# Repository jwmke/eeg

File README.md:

# Open-Source Affordable EEG PCB

### An 8-channel EEG Pi Pico W shield, based off of OpenBCI's [Cyton Biosensing Board](https://shop.openbci.com/products/cyton-biosensing-board-8-channel), for 1/10th the price.

The heart of this PCB is a Texas Instrument's [ADS1299](https://www.ti.com/product/ADS1299), a low noise, 8-Channel, Analog-to-Digital Converter.

## Instructions
1. Update your SSID and PASSWORD in the pico/main.py file
2. Upload the main.py to the Pi Pico W
3. Run the pico/main.py on the Pico Pi W and note the printed IP
5. Unplug the Pi Pico W from the PC and place it into the PCB
6. Update the PICO_IP in the computer/plot_data.py file
7. Run the computer/plot_data.py on a PC
8. Plug a 3.7V Lipo battery into the PCB
9. Blinking LED == Connecting, Solid LED == Succesfully streaming to PC

## Schematics

## Layout

Top

Bottom

Ground

AVSS/-2.5V

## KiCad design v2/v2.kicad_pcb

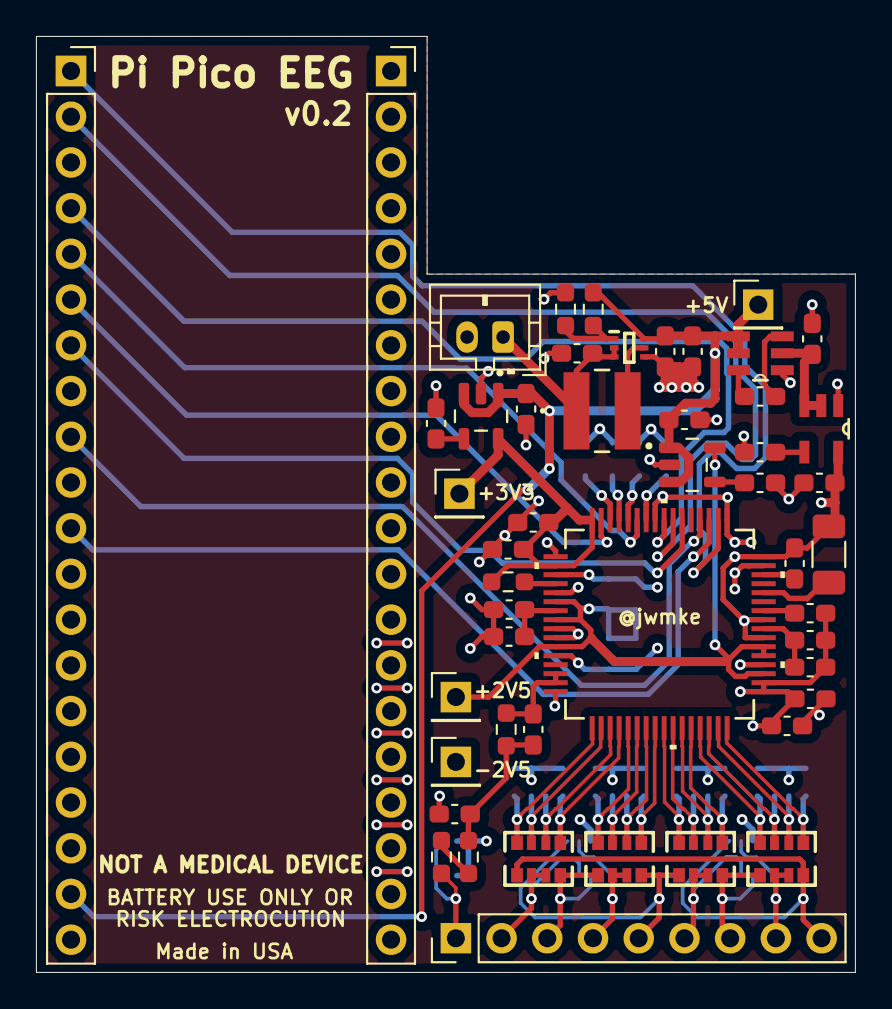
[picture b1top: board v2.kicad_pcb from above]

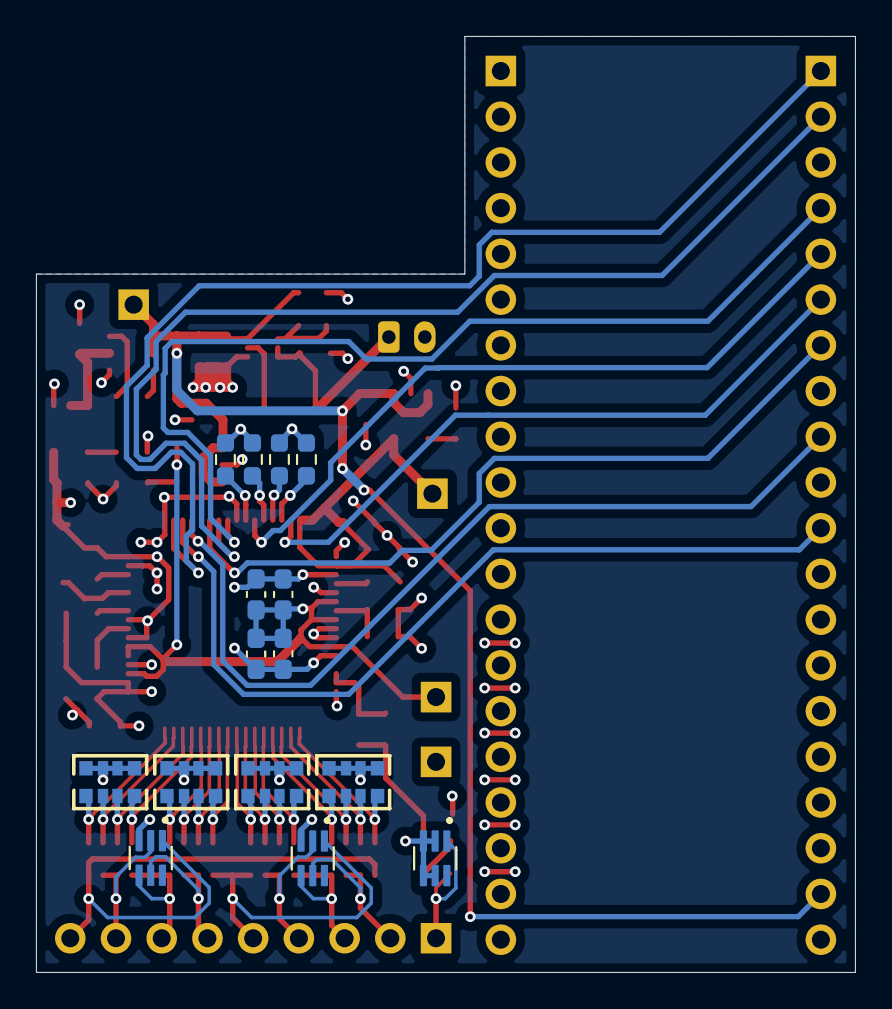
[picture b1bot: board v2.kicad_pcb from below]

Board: 4 copper layers, 45.5 x 52.0 mm, 64 parts (15 on the bottom side), 60 nets.

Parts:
C1: 1.5nF; C_0603_1608Metric_Pad1.08x0.95mm_HandSolder
C2, C6, C8, C11, C15, C16: 0.1µF; C_0603_1608Metric_Pad1.08x0.95mm_HandSolder
C3, C18, C19, C22: 10µF; C_0603_1608Metric_Pad1.08x0.95mm_HandSolder
C4, C5, C9, C10, C12, C14, C17, C27, C29: 1µF; C_0603_1608Metric_Pad1.08x0.95mm_HandSolder
C7: 1nF; C_0603_1608Metric_Pad1.08x0.95mm_HandSolder
C13: 100µF; C_1206_3216Metric_Pad1.33x1.80mm_HandSolder
C20, C21, C24: 22µF; C_0603_1608Metric_Pad1.08x0.95mm_HandSolder
C23, C28, C30: 0.01µF; C_0603_1608Metric_Pad1.08x0.95mm_HandSolder
CN1, CN2, CN3, CN4: W2A41C681KAT2A; CAP-ARRAY-SMD_6124-8P-L3.2-W1.6-BL
J1: Conn_01x02_Pin; JST_PH_B2B-PH-K_1x02_P2.00mm_Vertical
J2: Conn_01x09_Pin; PinHeader_1x09_P2.54mm_Vertical
J3, J4: Conn_01x20_Socket; PinSocket_1x20_P2.54mm_Vertical
J5, J6, J7, J8: Conn_01x01_Pin; PinHeader_1x01_P2.54mm_Vertical
L1: 1µH; IND_74438357010_WRE
R1: 1MΩ; R_0603_1608Metric_Pad0.98x0.95mm_HandSolder
R2, R3, R6, R7, R8, R9, R10: 10kΩ; R_0603_1608Metric_Pad0.98x0.95mm_HandSolder
R4: 732kΩ; R_0603_1608Metric_Pad0.98x0.95mm_HandSolder
R5: 100kΩ; R_0603_1608Metric_Pad0.98x0.95mm_HandSolder
RN5, RN6, RN7, RN8: CAY16-103J4LF; RES-ARRAY-SMD_0603-8P-L3.2-W1.6-BL
U1: ADS1299IPAGR; PAG64_TEX
U3, U4, U9: TPD4E1B06DCKR; tpd4e1b06dckr
U5: LM2664M6; lm266
U6: TPS61023DRLR; SOTFL50P160X60-6N
U7: TPS73233DBVT; 73233
U8: TPS72325DBVT; 72325
U11: TPS73225DBVR; 73225

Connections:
+2V5: C4.1, C6.1, C10.1, C11.1, J8.1, U1.19 (AVDD), U1.21 (AVDD), U1.22 (AVDD), U1.54 (AVDD1), U1.56 (AVDD), U1.59 (AVDD), U11.5 (OUT)
+3V3: C16.1, C17.1, J7.1, R6.1, U1.48 (DVDD), U1.50 (DVDD), U7.5 (OUT)
+5V: C20.2, C21.2, C27.2, C29.2, J3.19, J5.1, R4.1, U5.4 (~SD), U5.5 (V+), U6.6 (VOUT), U7.1 (IN), U7.3 (EN), U11.1 (IN), U11.3 (EN)
-2V5: C2.1, C3.2, C5.2, C8.1, C9.1, C10.2, C11.2, C12.2, C13.2, C14.1, C15.1, C24.2, J6.1, U1.17 (SRB1), U1.18 (SRB2), U1.20 (AVSS), U1.23 (AVSS), U1.25 (VREFN), U1.32 (AVSS), U1.53 (AVSS1), U1.57 (AVSS), U1.58 (AVSS), U1.60 (BIASREF), U8.5 (OUT)
-5V: C22.2, U5.2 (OUT), U8.2 (IN), U8.3 (EN)
/ADS1299/BI: J2.1, R2.2, U9.1 (IO1)
/ADS1299/Bias: C1.2, C7.1, R1.2, R10.1
/ADS1299/CS: J3.2, U1.39 (*CS)
/ADS1299/DRDY: J3.6, U1.47 (*DRDY)
/ADS1299/I1: J2.9, RN5.1, RN8.4, U3.1 (IO1)
/ADS1299/I2: J2.8, RN8.2, RN8.3, U3.2 (IO2)
/ADS1299/I3: J2.7, RN7.4, RN8.1, U3.4 (IO3)
/ADS1299/I4: J2.6, RN7.2, RN7.3, U3.5 (IO4)
/ADS1299/I5: J2.5, RN6.4, RN7.1, U4.1 (IO1)
/ADS1299/I6: J2.4, RN6.2, RN6.3, U4.2 (IO2)
/ADS1299/I7: J2.3, RN5.4, RN6.1, U4.4 (IO3)
/ADS1299/I8: J2.2, RN5.2, RN5.3, U4.5 (IO4)
/ADS1299/IN1N: CN1.2, RN8.6, U1.15 (IN1N)
/ADS1299/IN1P: CN1.1, RN8.5, U1.16 (IN1P)
/ADS1299/IN2N: CN1.4, RN8.8, U1.13 (IN2N)
/ADS1299/IN2P: CN1.3, RN8.7, U1.14 (IN2P)
/ADS1299/IN3N: CN2.2, RN7.6, U1.11 (IN3N)
/ADS1299/IN3P: CN2.1, RN7.5, U1.12 (IN3P)
/ADS1299/IN4N: CN2.4, RN7.8, U1.9 (IN4N)
/ADS1299/IN4P: CN2.3, RN7.7, U1.10 (IN4P)
/ADS1299/IN5N: CN3.2, RN6.6, U1.7 (IN5N)
/ADS1299/IN5P: CN3.1, RN6.5, U1.8 (IN5P)
/ADS1299/IN6N: CN3.4, RN6.8, U1.5 (IN6N)
/ADS1299/IN6P: CN3.3, RN6.7, U1.6 (IN6P)
/ADS1299/IN7N: CN4.2, RN5.6, U1.3 (IN7N)
/ADS1299/IN7P: CN4.1, RN5.5, U1.4 (IN7P)
/ADS1299/IN8N: CN4.4, RN5.8, U1.1 (IN8N)
/ADS1299/IN8P: CN4.3, RN5.7, U1.2 (IN8P)
/ADS1299/MISO: J3.5, U1.43 (DOUT)
/ADS1299/MOSI: J3.1, U1.34 (DIN)
/ADS1299/PDWN: J3.11, U1.35 (*PWDN)
/ADS1299/RESET: J3.9, U1.36 (*RESET)
/ADS1299/SCLK: J3.4, U1.40 (SCLK)
/ADS1299/START: J3.7, U1.38 (START)
/Booster/VBATT: C19.1, J1.1, L1.1, U6.2 (EN), U6.3 (VIN)
GND: C4.2, C6.2, C7.2, C14.2, C15.2, C16.2, C17.2, C19.2, C20.1, C21.1, C22.1, C23.1, C24.1, C27.1, C28.1, C29.1, C30.1, CN1.5, CN1.6, CN1.7, CN1.8, CN2.5, CN2.6, CN2.7, CN2.8, CN3.5, CN3.6, CN3.7, CN3.8, CN4.5, CN4.6, CN4.7, CN4.8, J1.2, J3.18, R3.2, R5.2, R7.2, R8.2, R9.2, U1.31 (RESV1), U1.33 (DGND), U1.41 (DAISY_IN), U1.49 (DGND), U1.51 (DGND), U1.64 (RESERVED), U3.3 (GND), U4.3 (GND), U5.1 (GND), U6.4 (GND), U7.2 (GND), U8.1 (GND), U9.2 (IO2), U9.3 (GND), U9.4 (IO3), U9.5 (IO4), U11.2 (GND)
unnamed: R2.1, R10.2
unnamed: C1.1, R1.1, U1.62 (BIASIN), U1.63 (BIASOUT)
unnamed: R6.2, U1.52 (CLKSEL)
unnamed: R3.1, U1.42 (GPIO1)
unnamed: R7.1, U1.44 (GPIO2)
unnamed: R8.1, U1.45 (GPIO3)
unnamed: R9.1, U1.46 (GPIO4)
unnamed: C13.1, U1.28 (VCAP1)
unnamed: C12.1, U1.30 (VCAP2)
unnamed: C8.2, C9.2, U1.55 (VCAP3)
unnamed: C5.1, U1.26 (VCAP4)
unnamed: C2.2, C3.1, U1.24 (VREFP)
unnamed: C18.1, U5.6 (CAP+)
unnamed: C18.2, U5.3 (CAP-)
unnamed: R4.2, R5.1, U6.1 (FB)
unnamed: L1.2, U6.5 (SW)
unnamed: C28.2, U7.4 (NR/FB)
unnamed: C23.2, U8.4 (NR)
unnamed: C30.2, U11.4 (NR/FB)

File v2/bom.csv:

"Id";"Designator";"Footprint";"Quantity";"Designation";"Supplier and ref";
1;"C22,C19,C18,C3";"C_0603_1608Metric_Pad1.08x0.95mm_HandSolder";4;"10µF ";;;
2;"R9,R7,R8,R3,R10,R6,R2";"R_0603_1608Metric_Pad0.98x0.95mm_HandSolder";7;"10kΩ";;;
3;"U11";"73225";1;"TPS73225DBVR";;;
4;"U9,U4,U3";"tpd4e1b06dckr";3;"TPD4E1B06DCKR";;;
5;"U8";"72325";1;"TPS72325DBVT";;;
6;"U7";"73233";1;"TPS73233DBVT";;;
7;"U6";"SOTFL50P160X60-6N";1;"TPS61023DRLR";;;
8;"U5";"lm266";1;"LM2664M6";;;
9;"RN8,RN7,RN6,RN5";"RES-ARRAY-SMD_0603-8P-L3.2-W1.6-BL";4;"CAY16-103J4LF";;;
10;"R5";"R_0603_1608Metric_Pad0.98x0.95mm_HandSolder";1;"100kΩ";;;
11;"R4";"R_0603_1608Metric_Pad0.98x0.95mm_HandSolder";1;"732kΩ";;;
12;"R1";"R_0603_1608Metric_Pad0.98x0.95mm_HandSolder";1;"1MΩ";;;
13;"L1";"IND_74438357010_WRE";1;"1µH";;;
14;"J1";"JST_PH_B2B-PH-K_1x02_P2.00mm_Vertical";1;"Conn_01x02_Pin";;;
15;"C30,C28,C23";"C_0603_1608Metric_Pad1.08x0.95mm_HandSolder";3;"0.01µF ";;;
16;"C29,C27,C17,C14,C10,C4,C12,C5,C9";"C_0603_1608Metric_Pad1.08x0.95mm_HandSolder";9;"1µF ";;;
17;"C24,C21,C20";"C_0603_1608Metric_Pad1.08x0.95mm_HandSolder";3;"22µF ";;;
18;"C16,C15,C11,C6,C2,C8";"C_0603_1608Metric_Pad1.08x0.95mm_HandSolder";6;"0.1µF ";;;
19;"C7";"C_0603_1608Metric_Pad1.08x0.95mm_HandSolder";1;"1nF";;;
20;"C1";"C_0603_1608Metric_Pad1.08x0.95mm_HandSolder";1;"1.5nF";;;
21;"CN4,CN3,CN2,CN1";"CAP-ARRAY-SMD_6124-8P-L3.2-W1.6-BL";4;"W2A41C681KAT2A";;;
22;"J3,J4";"PinSocket_1x20_P2.54mm_Vertical";2;"Conn_01x20_Socket";;;
23;"J2";"PinHeader_1x09_P2.54mm_Vertical";1;"Conn_01x09_Pin";;;
24;"U1";"PAG64_TEX";1;"ADS1299IPAGR";;;
25;"C13";"C_1206_3216Metric_Pad1.33x1.80mm_HandSolder";1;"100µF ";;;

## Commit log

2024-07-11 kicad project init
2024-07-11 import ads1299
2024-07-12 adding vcaps
2024-07-13 moving vcaps
2024-07-14 esp32 to pi pico
2024-07-14 vref pins
2024-07-15 ads1299 symbol planning
2024-07-16 ads1299 final symbol plan
2024-07-17 adding back INxN channels
2024-07-17 avss avdd connections
2024-07-17 dvdd clk and clksel
2024-07-18 first input schem draft
2024-07-19 input cp
2024-07-20 input offset montage
2024-07-20 duplicate input
2024-07-20 bias input draft
2024-07-20 volt regs
2024-07-21 booster and voltage regulators
2024-07-22 v0.1 schematic finishing touches
2024-07-22 removed old input schem
2024-07-23 avss adjustments
2024-07-23 ground unused gpio
2024-07-24 simplifying inputs
2024-07-27 power on own sheet
2024-07-27 volt reg to power page
2024-07-29 other pages for volt regs
2024-07-29 connecting volt regs
2024-07-29 RP2040 sheet
2024-07-29 ads1299 sheet
2024-07-29 root page org
2024-07-30 ads1299 layout change
2024-07-31 start of footprints
2024-07-31 more footprints
2024-07-31 cap footprints finished
2024-07-31 cap and resis array footprints
2024-08-01 res footprints
2024-08-01 final footprints
2024-08-01 initial pcb import
2024-08-01 pi socket spacing
2024-08-01 begining traces
2024-08-02 v0.1, pre-grounding
2024-08-03 layout additions
2024-08-06 v2 template
2024-08-07 fix bias
2024-08-08 footprint reset for v0.2
2024-08-08 new footprints
2024-08-08 v02 init placements
2024-08-09 v2 volt regs and grounding
2024-08-10 layout reorg
2024-08-10 test pins
2024-08-12 final v02
2024-11-26 v2 code
2024-11-26 gitignore change
2024-11-26 removed scs
2024-11-26 kicad deletions
2024-11-29 blink test
2024-11-30 firmware attempt 1
2024-11-30 experimentation
